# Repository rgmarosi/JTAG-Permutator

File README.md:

# JTAG-Permutator
A low-cost USB tool for identifying pinouts of possible JTAG programming/debug interfaces on electronics.

## License
The JTAG Permutator is an adaptation of the "[JTAGulator](https://github.com/grandideastudio/jtagulator)" designed by Joe Grand of [Grand Idea Studio](http://www.grandideastudio.com/) and is used under the [Creative Commons Attribution 3.0 United States license](https://creativecommons.org/licenses/by/3.0/us/).

The JTAG Permutator design is also distributed under the [Creative Commons Attribution 3.0 United States license](https://creativecommons.org/licenses/by/3.0/us/).

### Major changes from the JTAGulator design
1. Silicon Labs EFM8 microcontroller used instead of Parallax microcontroller with USB-UART bridge IC
2. Target voltage supplied by SC195 buck regulator rather than filtered PWM
3. Removed screw terminals
4. Reduced IO channels from 24 down to 8
5. Used different level translator IC (target voltage range is now 0.8V~3.3V) (to be verified)
6. Reduced board area from 13.6 square inches down to 1.7 square inches

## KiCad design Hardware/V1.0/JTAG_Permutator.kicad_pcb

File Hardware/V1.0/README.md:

# Notes
- IDC headers are not placed in BOM because fab & assembly is cheaper with all SMD components. They can be easily hand-soldered.
- The JTAG Permutator is compatible with [Bus Pirate V3 probes](https://www.seeedstudio.com/Bus-Pirate-v3-probe-Kit-p-526.html) or equivalent.
- The programmer interface requires a stronger 1kOhm pull-up resistor on the reset pin in order for the debug adapter to remain connected to the JTAG Permutator
  - Solder a 1kOhm resistor between TP1 and TP5 on the rear of the board to fix this
- The programmer used with the programmer header is the Silicon Labs [8-bit USB Debug Adapter](https://www.silabs.com/products/development-tools/mcu/8-bit/8bit-mcu-accessories/8-bit-debug-adapter)
  - The programmer header may not be needed if I can figure out how to use the bootloader on the EFM8. Until then, it's there for easy debugging of this first prototype.
- The fab & assembly house I used for this first prototype was [MacroFab](https://macrofab.com/). Another good self-serve fab & assembly house is [PCB:NG](https://www.pcb.ng/).
- I don't yet know if the onboard buck regulator (SC195) output is tri-stated when disabled. I need to test it. For now, don't connect the target power rail to powered targets. Only use it if you're powering the target using the JTAG Permutator.
  - Maximum current output of the buck regulator is ~500mA.
## Pull-up resistor fix

# Planned changes
1. Pull up C2CK pin of microcontroller to 5V rail using 1kOhm resistor.
2. Remove programming header once bootloader is figured out and firmware is functioning as intended. Keep C2 interface and power rail test points.
3. Add silkscreen pin table for probe cable if space permits.
4. More to come...

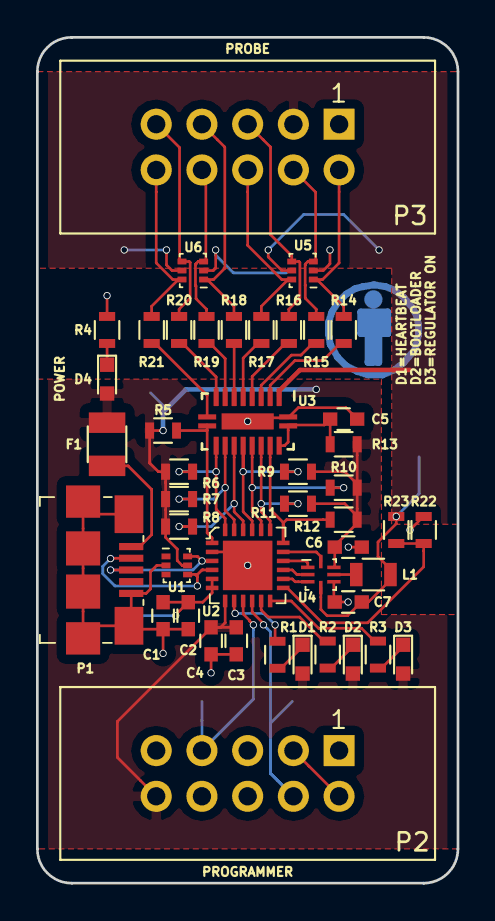
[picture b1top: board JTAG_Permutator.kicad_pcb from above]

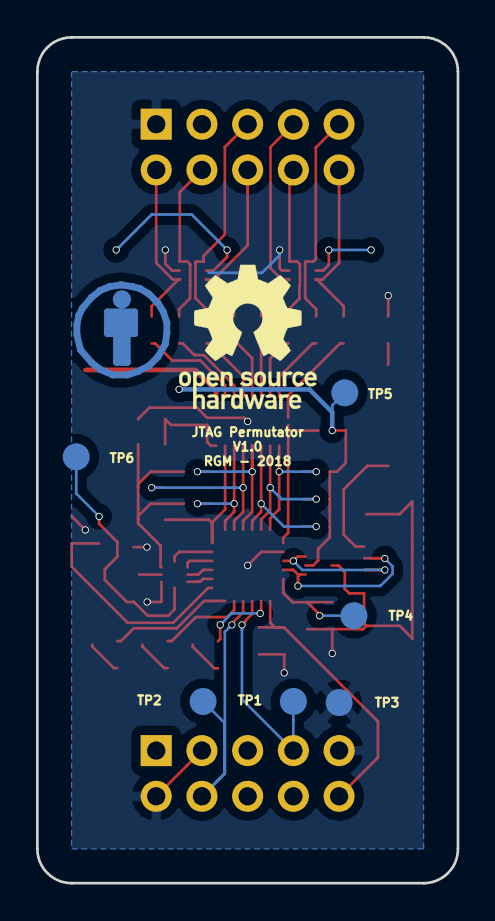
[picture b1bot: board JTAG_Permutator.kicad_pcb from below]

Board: 2 copper layers, 23.4 x 47.0 mm, 51 parts (6 on the bottom side), 47 nets.

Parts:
C1, C3, C6: 4.7uF; C_0603
C2, C4, C5: 0.1uF; C_0603
C7: 10uF; C_0603
D1: LED_Heartbeat; LED_0603
D2: LED_BOOT; LED_0603
D3: LED_PWR; LED_0603
D4: LED_ON; LED_0603
F1: 500mA PTC; Fuse_SMD1206_Reflow
L1: 1uH; L_0805
P1: USB_OTG; 609-4613-1-ND
P2: Debug Adapter Connector; IDC-Header_2x05_Pitch2.54mm_Straight
P3: Bus Pirate Probe Cable Connector; IDC-Header_2x05_Pitch2.54mm_Straight
R1, R2, R3, R4, R22, R23: 1k; R_0603
R5, R6, R7, R8, R9, R10, R11, R12, R14, R15, R16, R17, R18, R19, R20, R21: 470R; R_0603
R13: 200k; R_0603
TP1, TP2, TP3, TP4, TP5, TP6: TEST; Measurement_Point_Round-SMD-Pad_Small
U1, U5, U6: DT1446-04V-7; SOT563
U2: EFM8UB31F40G-A; 24-WQFN_(4x4)
U3: GTL2003BQ_115; DHVQFN20
U4: SC195; MLPQ-UT8

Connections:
+5V: C3.1, C4.1, C6.2, D1.2, D2.2, D3.2, D4.2, F1.1, P2.10, R5.1, R6.1, R7.1, R8.1, R9.1, R10.1, R11.1, R12.1, R13.1, TP5.1, U1.5, U2.7, U4.7
/ADC_Target: R22.2, R23.1, U2.13
/C2CK: P2.7, TP1.1, U2.9
/C2D: P2.4, TP2.1, U2.10
/CH1: P3.2, R14.1, U5.1
/CH2: P3.4, R15.1, U5.3
/CH3: P3.5, R16.1, U5.4
/CH4: P3.6, R17.1, U5.6
/CH5: P3.7, R18.1, U6.1
/CH6: P3.8, R19.1, U6.3
/CH7: P3.9, R20.1, U6.4
/CH8: P3.10, R21.1, U6.6
/CTL0: U2.14, U4.3
/CTL1: U2.15, U4.2
/CTL2: U2.16, U4.1
/CTL3: U2.17, U4.8
/D1: R12.2, U2.18, U3.18
/D2: R11.2, U2.19, U3.17
/D3: R10.2, U2.20, U3.16
/D4: R9.2, U2.21, U3.15
/D5: R8.2, U2.22, U3.14
/D6: R7.2, U2.23, U3.13
/D7: R6.2, U2.24, U3.12
/D8: R5.2, U2.1, U3.11
/D+: P1.3, U1.6, U2.3
/D-: P1.2, U1.4, U2.4
/LED_BL: R2.2, U2.11
/LED_Heartbeat: R1.2, U2.8
/LED_PWR_ON: R3.2, U2.12
/VIO: C1.1, C2.1, TP4.1, U2.5, U2.6
/V_Target: C7.1, L1.2, P3.3, R22.1, TP6.1, U3.2, U4.4, U5.5, U6.5
GND: C1.2, C2.2, C3.2, C4.2, C5.2, C6.1, C7.2, P1.5, P1.6, P2.2, P2.3, P2.9, P3.1, R4.2, R23.2, TP3.1, U1.2, U2.2, U2.25, U3.1, U3.21, U4.5, U5.2, U6.2
unnamed: C5.1, R13.2, U3.19, U3.20
unnamed: D1.1, R1.1
unnamed: D2.1, R2.1
unnamed: D3.1, R3.1
unnamed: D4.1, R4.1
unnamed: F1.2, P1.1
unnamed: L1.1, U4.6
unnamed: R14.2, U3.3
unnamed: R15.2, U3.4
unnamed: R16.2, U3.5
unnamed: R17.2, U3.6
unnamed: R18.2, U3.7
unnamed: R19.2, U3.8
unnamed: R20.2, U3.9
unnamed: R21.2, U3.10

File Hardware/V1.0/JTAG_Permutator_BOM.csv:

Title,JTAG Permutator,,,,,,,
Revision,1,,,,,,,
Date,2/6/2018,,,,,,,
Generated,2/6/2018 16:55,,,,,,,
Company,,,,,,,,
Comment 1,Robert Marosi,,,,,,,
Comment 2,CC BY 3.0 US,,,,,,,
Comment 3,,,,,,,,
Comment 4,,,,,,,,
Total Parts,43,,,,,,,
Total Unique Parts,20,,,,,,,
,,,,,,,,
,,,,,,,,
,,,,,,,,
Ref,Qty,Value,Footprint,MFR,MPN,SPN,SPR,DNI
C7 ,1,10uF,Capacitors_SMD:C_0603,TDK Corporation,C1608X5R0J106M080AB,445-4112-2-ND,Digi-Key,
C6 C3 C1 ,3,4.7uF,Capacitors_SMD:C_0603,Murata,GRM188R60J475ME19D,490-5421-2-ND,Digi-Key,
C5 C4 C2 ,3,0.1uF,Capacitors_SMD:C_0603,Murata,GRM188R71E104KA01, 490-1524-2-ND,Digi-Key,
D4 ,1,LED_ON,LEDs:LED_0603,Lite-On Inc.,LTST-C190KRKT,160-1436-2-ND,Digi-Key,
D3 ,1,LED_PWR,LEDs:LED_0603,Lite-On Inc.,LTST-C190KRKT,160-1436-2-ND,Digi-Key,
D2 ,1,LED_BOOT,LEDs:LED_0603,Lite-On Inc.,LTST-C190KRKT,160-1436-2-ND,Digi-Key,
D1 ,1,LED_Heartbeat,LEDs:LED_0603,Lite-On Inc.,LTST-C190KRKT,160-1436-2-ND,Digi-Key,
F1 ,1,500mA PTC,Fuse_Holders_and_Fuses:Fuse_SMD1206_Reflow,Bel Fuse Inc.,0ZCJ0050FF2G,507-1802-1-ND ,Digi-Key,
L1 ,1,1uH,Inductors_SMD:L_0805,Taiyo Yuden,MBKK2012T1R0M,587-4156-2-ND,Digi-Key,
P3 ,0,Bus Pirate Probe Cable Connector,Connectors_IDC:IDC-Header_2x05_Pitch2.54mm_Straight,On Shore Technology Inc.,302-S101,ED1543-ND,Digi-Key,P3
P2 ,0,Debug Adapter Connector,Connectors_IDC:IDC-Header_2x05_Pitch2.54mm_Straight,On Shore Technology Inc.,302-S101,ED1543-ND,Digi-Key,P2
P1 ,1,USB_OTG,digikey-footprints:609-4613-1-ND,Amphenol FCI,10118192-0001LF,609-4613-1-ND,Digi-Key,
R13 ,1,200k,Resistors_SMD:R_0603,TE Connectivity Passive Product,CPF0603F200KC1,A102235TR-ND ,Digi-Key,
R22 R23 R1 R2 R3 R4 ,6,1k,Resistors_SMD:R_0603,Panasonic Electronics Components,ERJ-3GEYJ102V,P1.0KGTR-ND,Digi-Key,
R5 R6 R7 R8 R9 R10 R11 R12 R14 R15 R16 R17 R18 R19 R20 R21 ,16,470R,Resistors_SMD:R_0603,Yageo,RC0603JR-07470RL,311-470GRTR-ND,Digi-Key,
TP1 TP2 TP3 TP4 TP5 TP6 ,0,TEST,Measurement_Points:Measurement_Point_Round-SMD-Pad_Small,N/A,N/A,N/A,N/A,TP1 TP2 TP3 TP4 TP5 TP6 
U3 ,1,GTL2003BQ_115,GTL2003:DHVQFN20,NXP USA Inc.,GTL2003BQ 115,568-4293-1-ND,Digi-Key,
U4 ,1,SC195,SC195:MLPQ-UT8,Semtech Corporation,SC195ULTRT,SC195ULTR-ND,Digi-Key,
U1 U5 U6 ,3,DT1446-04V-7,DT1446-04V-7:SOT563,Diodes Inc.,DT1446-04V-7,DT1446-04V-7DITR-ND,Digi-Key,
U2 ,1,EFM8UB31F40G-A,digikey-footprints:24-WQFN_(4x4),Silicon Labs,EFM8UB31F40G-A-QFN24,336-4232-ND,Digi-Key,
,,,,,,,,
,,,,,,,,
,,,,,,,,
,,,,,,,,
BOM made with KICAD_BOM_WIZARD (https://github.com/HashDefineElectronics/KiCad_BOM_Wizard.git),,,,,,,,
Generated 2/6/2018 4:55:48 PM,,,,,,,,

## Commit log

2018-02-07 Uploaded Fab & Assembly Files
2018-02-07 Update README.md
    Added photos of PCB
2018-02-07 Add Firmware Folder
2018-02-07 Update README.md
    Added photo with probes
2018-02-07 Update README.md
    added pull-up resistor fix photo
2018-03-18 Added Hello World Project
